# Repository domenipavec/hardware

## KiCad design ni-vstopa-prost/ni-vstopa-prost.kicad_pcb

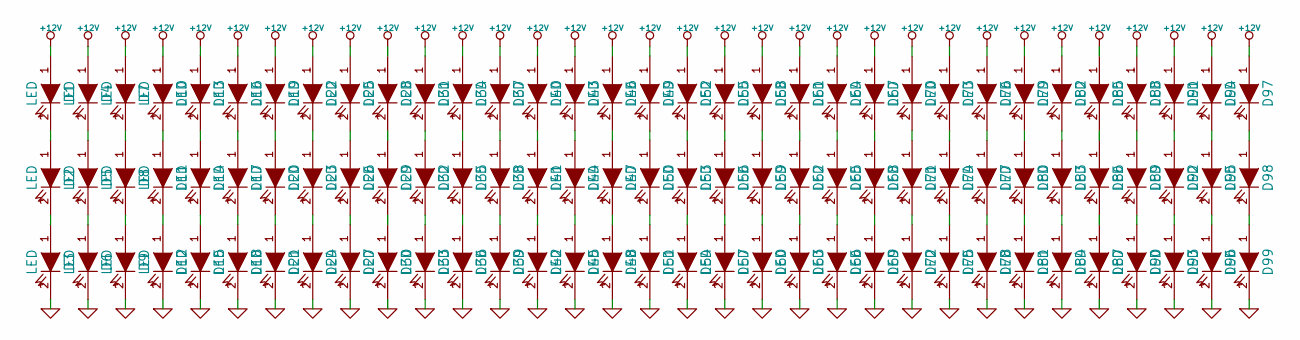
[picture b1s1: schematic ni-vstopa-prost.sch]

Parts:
D1, D2, D3, D4, D5, D6, D7, D8, D9, D10, D11, D12, D13, D14, D15, D16, D17, D18, D19, D20, D21, D22, D23, D24, D25, D26, D27, D28, D29, D30, D31, D32, D33, D34, D35, D36, D37, D38, D39, D40, D41, D42, D43, D44, D45, D46, D47, D48, D49, D50, D51, D52, D53, D54, D55, D56, D57, D58, D59, D60, D61, D62, D63, D64, D65, D66, D67, D68, D69, D70, D71, D72, D73, D74, D75, D76, D77, D78, D79, D80, D81, D82, D83, D84, D85, D86, D87, D88, D89, D90, D91, D92, D93, D94, D95, D96, D97, D98, D99: LED

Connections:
+12V: D1.1 (A), D4.1 (A), D7.1 (A), D10.1 (A), D13.1 (A), D16.1 (A), D19.1 (A), D22.1 (A), D25.1 (A), D28.1 (A), D31.1 (A), D34.1 (A), D37.1 (A), D40.1 (A), D43.1 (A), D46.1 (A), D49.1 (A), D52.1 (A), D55.1 (A), D58.1 (A), D61.1 (A), D64.1 (A), D67.1 (A), D70.1 (A), D73.1 (A), D76.1 (A), D79.1 (A), D82.1 (A), D85.1 (A), D88.1 (A), D91.1 (A), D94.1 (A), D97.1 (A)
GND: D3.2 (K), D6.2 (K), D9.2 (K), D12.2 (K), D15.2 (K), D18.2 (K), D21.2 (K), D24.2 (K), D27.2 (K), D30.2 (K), D33.2 (K), D36.2 (K), D39.2 (K), D42.2 (K), D45.2 (K), D48.2 (K), D51.2 (K), D54.2 (K), D57.2 (K), D60.2 (K), D63.2 (K), D66.2 (K), D69.2 (K), D72.2 (K), D75.2 (K), D78.2 (K), D81.2 (K), D84.2 (K), D87.2 (K), D90.2 (K), D93.2 (K), D96.2 (K), D99.2 (K)
unnamed: D89.2 (K), D90.1 (A)
unnamed: D86.2 (K), D87.1 (A)
unnamed: D85.2 (K), D86.1 (A)
unnamed: D88.2 (K), D89.1 (A)
unnamed: D91.2 (K), D92.1 (A)
unnamed: D92.2 (K), D93.1 (A)
unnamed: D79.2 (K), D80.1 (A)
unnamed: D80.2 (K), D81.1 (A)
unnamed: D82.2 (K), D83.1 (A)
unnamed: D83.2 (K), D84.1 (A)
unnamed: D58.2 (K), D59.1 (A)
unnamed: D59.2 (K), D60.1 (A)
unnamed: D61.2 (K), D62.1 (A)
unnamed: D62.2 (K), D63.1 (A)
unnamed: D64.2 (K), D65.1 (A)
unnamed: D65.2 (K), D66.1 (A)
unnamed: D94.2 (K), D95.1 (A)
unnamed: D95.2 (K), D96.1 (A)
unnamed: D55.2 (K), D56.1 (A)
unnamed: D56.2 (K), D57.1 (A)
unnamed: D97.2 (K), D98.1 (A)
unnamed: D98.2 (K), D99.1 (A)
unnamed: D71.2 (K), D72.1 (A)
unnamed: D70.2 (K), D71.1 (A)
unnamed: D73.2 (K), D74.1 (A)
unnamed: D74.2 (K), D75.1 (A)
unnamed: D76.2 (K), D77.1 (A)
unnamed: D77.2 (K), D78.1 (A)
unnamed: D19.2 (K), D20.1 (A)
unnamed: D20.2 (K), D21.1 (A)
unnamed: D22.2 (K), D23.1 (A)
unnamed: D16.2 (K), D17.1 (A)
unnamed: D17.2 (K), D18.1 (A)
unnamed: D26.2 (K), D27.1 (A)
unnamed: D29.2 (K), D30.1 (A)
unnamed: D28.2 (K), D29.1 (A)
unnamed: D25.2 (K), D26.1 (A)
unnamed: D23.2 (K), D24.1 (A)
unnamed: D7.2 (K), D8.1 (A)
unnamed: D4.2 (K), D5.1 (A)
unnamed: D5.2 (K), D6.1 (A)
unnamed: D8.2 (K), D9.1 (A)
unnamed: D1.2 (K), D2.1 (A)
unnamed: D2.2 (K), D3.1 (A)
unnamed: D13.2 (K), D14.1 (A)
unnamed: D14.2 (K), D15.1 (A)
unnamed: D10.2 (K), D11.1 (A)
unnamed: D11.2 (K), D12.1 (A)
unnamed: D49.2 (K), D50.1 (A)
unnamed: D50.2 (K), D51.1 (A)
unnamed: D46.2 (K), D47.1 (A)
unnamed: D47.2 (K), D48.1 (A)
unnamed: D43.2 (K), D44.1 (A)
unnamed: D44.2 (K), D45.1 (A)
unnamed: D67.2 (K), D68.1 (A)
unnamed: D68.2 (K), D69.1 (A)
unnamed: D52.2 (K), D53.1 (A)
unnamed: D53.2 (K), D54.1 (A)
unnamed: D34.2 (K), D35.1 (A)
unnamed: D35.2 (K), D36.1 (A)
unnamed: D31.2 (K), D32.1 (A)
unnamed: D32.2 (K), D33.1 (A)
unnamed: D40.2 (K), D41.1 (A)
unnamed: D41.2 (K), D42.1 (A)
unnamed: D37.2 (K), D38.1 (A)
unnamed: D38.2 (K), D39.1 (A)

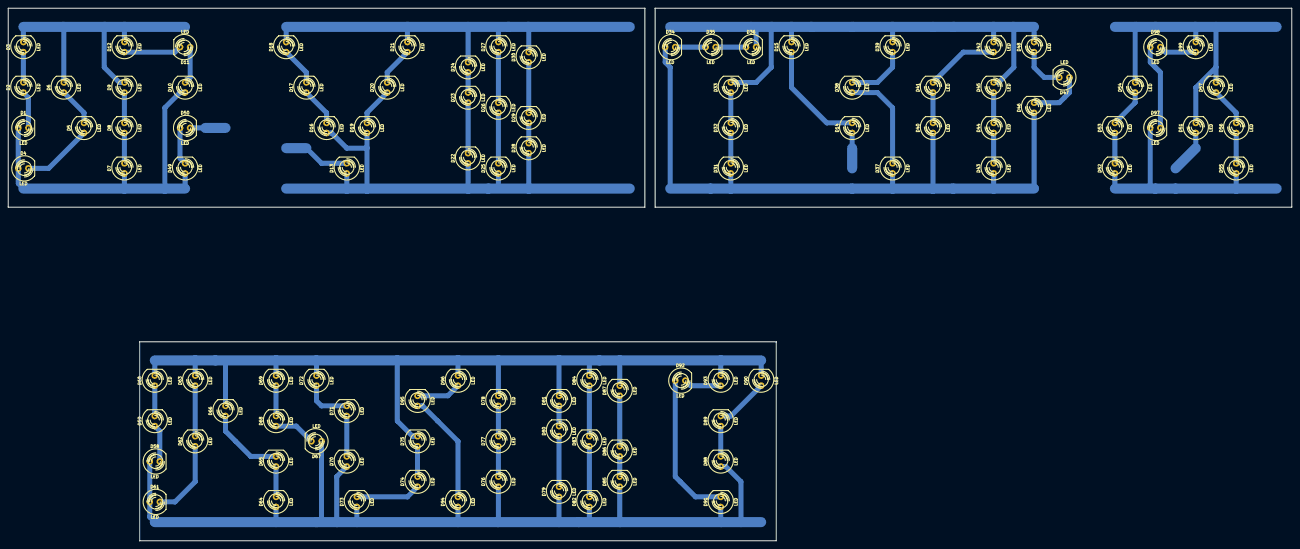
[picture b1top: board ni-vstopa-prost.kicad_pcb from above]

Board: 2 copper layers, 322.6 x 133.8 mm, 99 parts (0 on the bottom side), 68 nets.

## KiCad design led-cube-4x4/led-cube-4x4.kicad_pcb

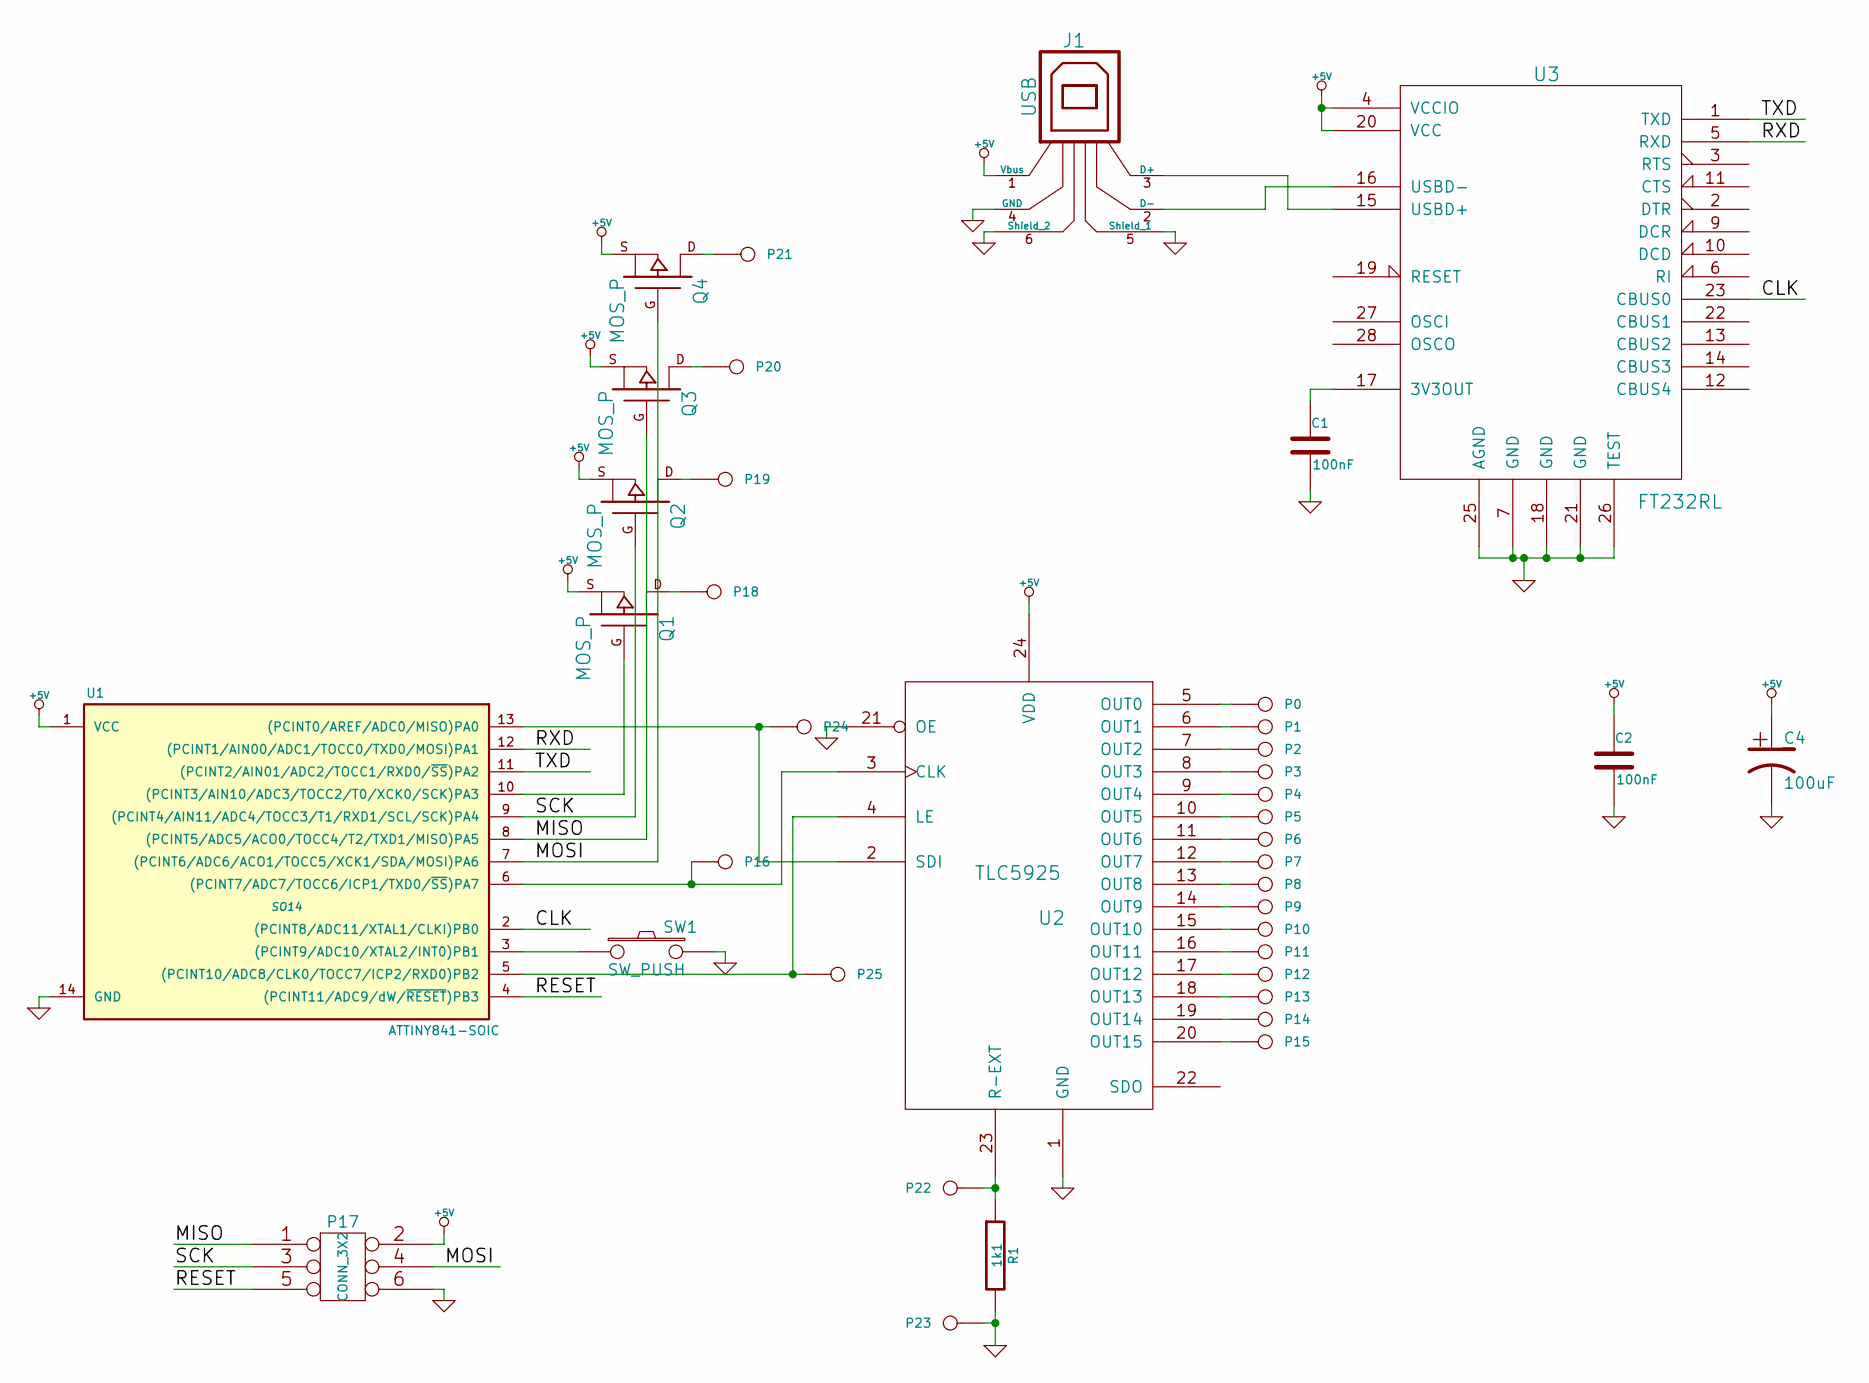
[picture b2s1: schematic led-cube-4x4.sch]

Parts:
C1, C2: 100nF
C4: 100uF
J1: USB
P0, P1, P2, P3, P4, P5, P6, P7, P8, P9, P10, P11, P12, P13, P14, P15, P16, P18, P19, P20, P21, P22, P23, P24, P25: CONN_1
P17: CONN_3X2; pin_array_3x2
Q1, Q2, Q3, Q4: MOS_P
R1: 1k1
SW1: SW_PUSH
U1: ATTINY841-SOIC; SO14
U2: TLC5925
U3: FT232RL

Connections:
+5V: C2.1, C4.1, J1.1 (Vbus), P17.2, Q1.S, Q2.S, Q3.S, Q4.S, U1.1 (VCC), U2.24 (VDD), U3.4 (VCCIO), U3.20 (VCC)
/CLK: U1.2 ((PCINT8/ADC11/XTAL1/CLKI)PB0), U3.23 (CBUS0)
/MISO: P17.1, Q3.G, U1.8 ((PCINT5/ADC5/ACO0/TOCC4/T2/TXD1/MISO)PA5)
/MOSI: P17.4, Q4.G, U1.7 ((PCINT6/ADC6/ACO1/TOCC5/XCK1/SDA/MOSI)P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)
/RESET: P17.5, U1.4 ((PCINT11/ADC9/dW/~RESET~)PB3)
/RXD: U1.12 ((PCINT1/AIN00/ADC1/TOCC0/TXD0/MOSI)PA1), U3.5 (RXD)
/SCK: P17.3, Q2.G, U1.9 ((PCINT4/AIN11/ADC4/TOCC3/T1/RXD1/SCL/SC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)
/TXD: U1.11 ((PCINT2/AIN01/ADC2/TOCC1/RXD0/~SS~)PA2), U3.1 (TXD)
GND: C1.2, C2.2, C4.2, J1.4 (GND), J1.5 (Shield_1), J1.6 (Shield_2), P17.6, P23.1, R1.2, SW1.2, U1.14 (GND), U2.1 (GND), U2.21 (OE), U3.7 (GND), U3.18 (GND), U3.21 (GND), U3.25 (AGND), U3.26 (TEST); also elsewhere on the board
unnamed: J1.3 (D+), U3.15 (USBD+)
unnamed: J1.2 (D-), U3.16 (USBD-)
unnamed: P24.1, U1.13 ((PCINT0/AREF/ADC0/MISO)PA0), U2.2 (SDI)
unnamed: P25.1, U1.5 ((PCINT10/ADC8/CLK0/TOCC7/ICP2/RXD0)PB2), U2.4 (LE)
unnamed: P0.1, U2.5 (OUT0)
unnamed: P1.1, U2.6 (OUT1)
unnamed: P2.1, U2.7 (OUT2)
unnamed: P3.1, U2.8 (OUT3)
unnamed: P4.1, U2.9 (OUT4)
unnamed: C1.1, U3.17 (3V3OUT)
unnamed: SW1.1, U1.3 ((PCINT9/ADC10/XTAL2/INT0)PB1)
unnamed: P16.1, U1.6 ((PCINT7/ADC7/TOCC6/ICP1/TXD0/~SS~)PA7), U2.3 (CLK)
unnamed: P5.1, U2.10 (OUT5)
unnamed: P19.1, Q2.D
unnamed: P18.1, Q1.D
unnamed: P22.1, R1.1, U2.23 (R-EXT)
unnamed: P9.1, U2.14 (OUT9)
unnamed: P8.1, U2.13 (OUT8)
unnamed: P7.1, U2.12 (OUT7)
unnamed: P6.1, U2.11 (OUT6)
unnamed: P15.1, U2.20 (OUT15)
unnamed: P10.1, U2.15 (OUT10)
unnamed: Q1.G, U1.10 ((PCINT3/AIN10/ADC3/TOCC2/T0/XCK0/SCK)PA3)
unnamed: P20.1, Q3.D
unnamed: P14.1, U2.19 (OUT14)
unnamed: P13.1, U2.18 (OUT13)
unnamed: P12.1, U2.17 (OUT12)
unnamed: P11.1, U2.16 (OUT11)
unnamed: P21.1, Q4.D

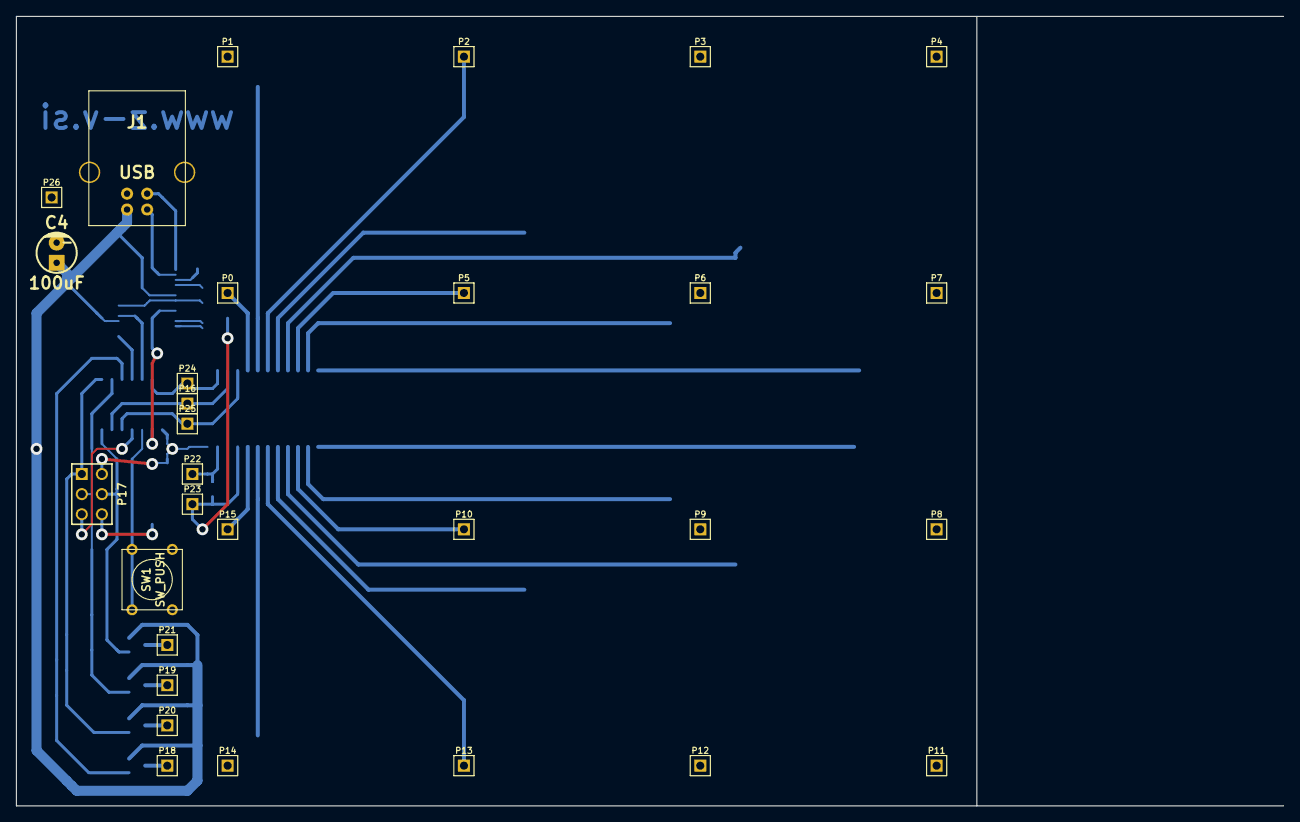
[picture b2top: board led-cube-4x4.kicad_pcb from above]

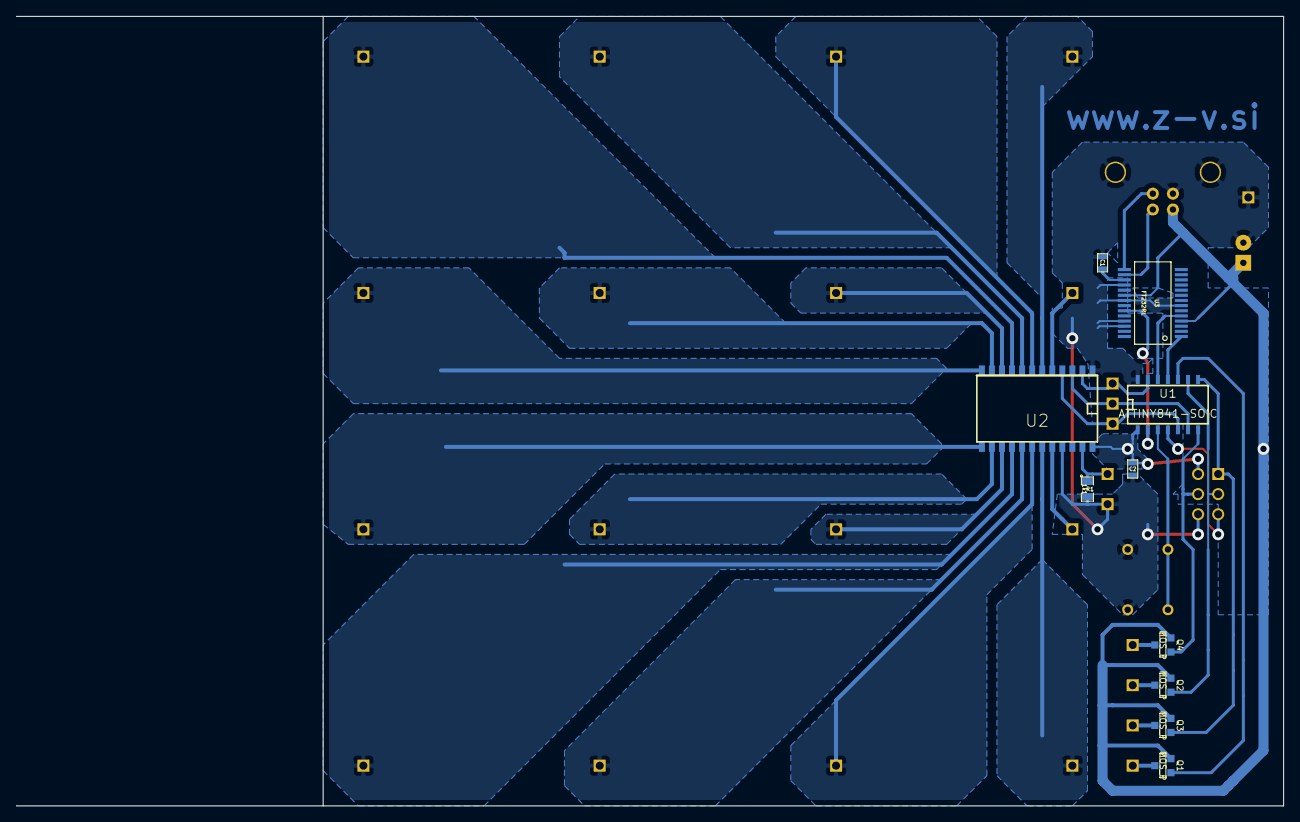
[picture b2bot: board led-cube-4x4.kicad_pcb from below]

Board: 2 copper layers, 160.0 x 99.7 mm, 40 parts (10 on the bottom side), 38 nets.

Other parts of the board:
P26: CONN_1; PIN_ARRAY_1

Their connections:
GND: P26.1; also elsewhere on the board

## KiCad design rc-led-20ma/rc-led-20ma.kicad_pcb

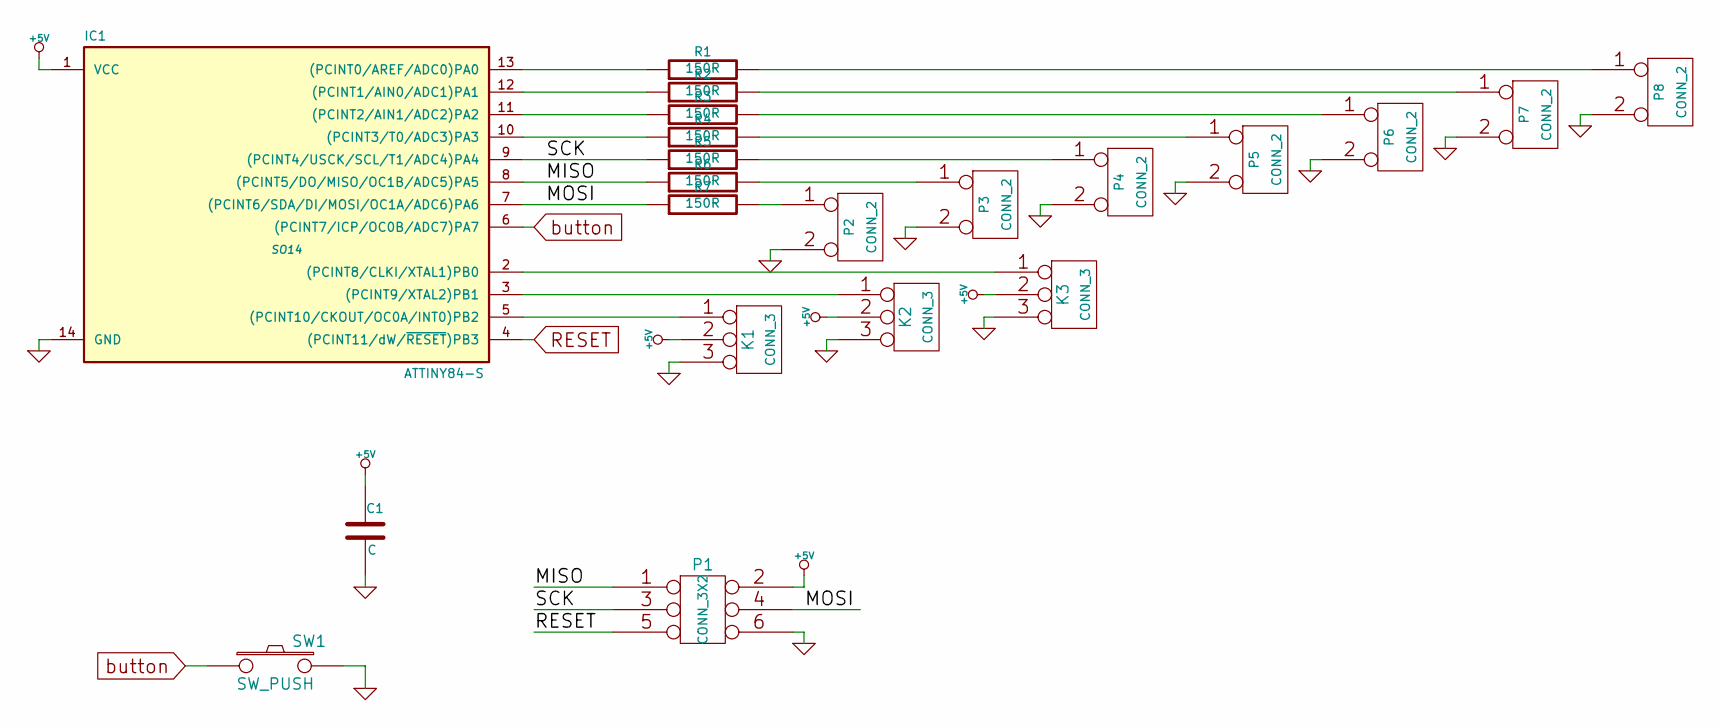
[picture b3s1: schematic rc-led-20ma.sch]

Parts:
C1: C
IC1: ATTINY84-S; SO14
K1, K2, K3: CONN_3; PIN_ARRAY_3X1
P1: CONN_3X2; pin_array_3x2
P2, P3, P4, P5, P6, P7, P8: CONN_2; PIN_ARRAY_2X1
R1, R2, R3, R4, R5, R6, R7: 150R
SW1: SW_PUSH; SW_PUSH-12mm

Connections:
+5V: C1.1, IC1.1 (VCC), K1.2 (PM), K2.2 (PM), K3.2 (PM), P1.2
/MISO: IC1.8 ((PCINT5/DO/MISO/OC1B/ADC5)PA5), P1.1, R6.1
/MOSI: IC1.7 ((PCINT6/SDA/DI/MOSI/OC1A/ADC6)PA6), P1.4, R7.1
/SCK: IC1.9 ((PCINT4/USCK/SCL/T1/ADC4)PA4), P1.3, R5.1
GND: C1.2, IC1.14 (GND), K1.3, K2.3, K3.3, P1.6, P2.2 (PM), P3.2 (PM), P4.2 (PM), P5.2 (PM), P6.2 (PM), P7.2 (PM), P8.2 (PM), SW1.2
unnamed: IC1.2 ((PCINT8/CLKI/XTAL1)PB0), K3.1
unnamed: IC1.3 ((PCINT9/XTAL2)PB1), K2.1
unnamed: P7.1, R2.2
unnamed: IC1.11 ((PCINT2/AIN1/ADC2)PA2), R3.1
unnamed: IC1.10 ((PCINT3/T0/ADC3)PA3), R4.1
unnamed: P2.1, R7.2
unnamed: P3.1, R6.2
unnamed: P4.1, R5.2
unnamed: P5.1, R4.2
unnamed: P6.1, R3.2
unnamed: IC1.12 ((PCINT1/AIN0/ADC1)PA1), R2.1
unnamed: P8.1, R1.2
unnamed: IC1.5 ((PCINT10/CKOUT/OC0A/INT0)PB2), K1.1
unnamed: IC1.13 ((PCINT0/AREF/ADC0)PA0), R1.1
RESET: IC1.4 ((PCINT11/dW/~RESET~)PB3), P1.5
button: IC1.6 ((PCINT7/ICP/OC0B/ADC7)PA7), SW1.1

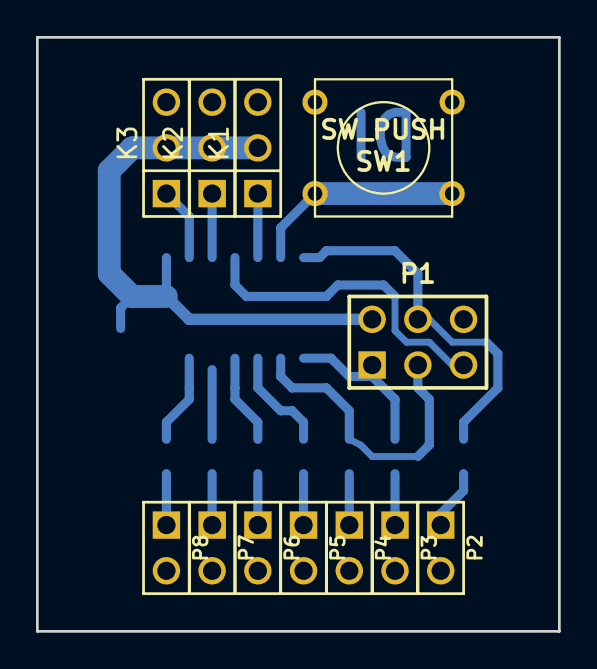
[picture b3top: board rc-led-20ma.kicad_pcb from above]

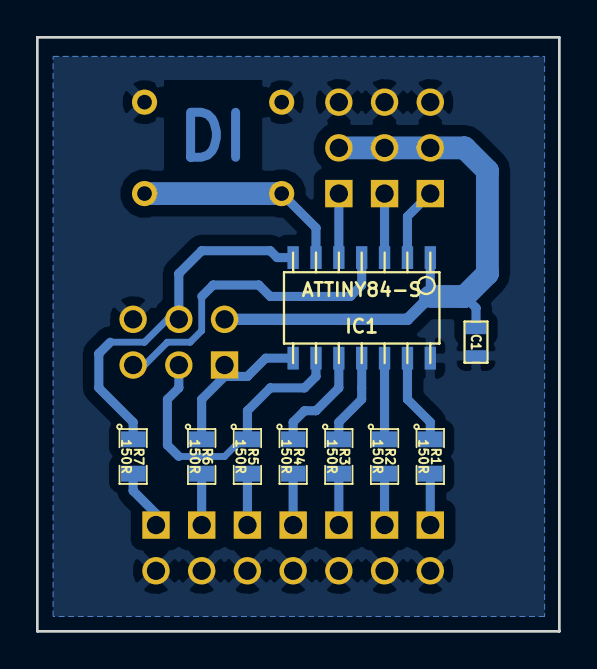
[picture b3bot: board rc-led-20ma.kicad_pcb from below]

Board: 2 copper layers, 29.0 x 33.0 mm, 21 parts (9 on the bottom side), 21 nets.

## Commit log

2014-11-28 Added LICENSE.
2014-11-30 Added rc-led-20ma.
2015-01-31 Led cube and library first commit.
2015-02-28 Better copper coverage on pcb.
2015-08-17 Two new projects.
